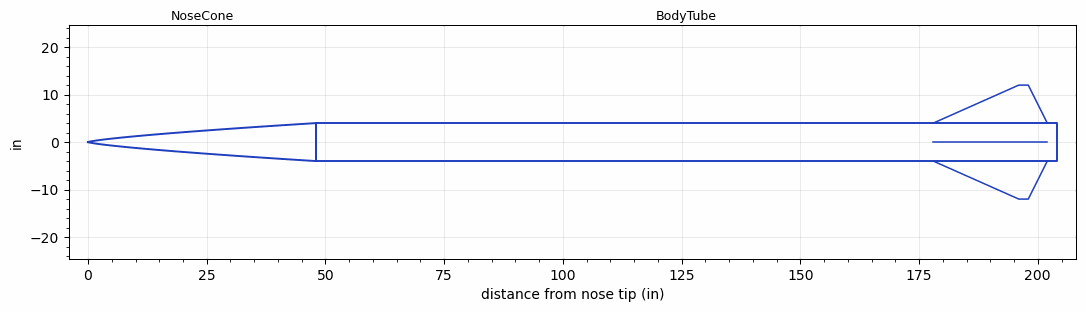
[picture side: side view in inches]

<RASAeroDocument>
 <FileVersion>2</FileVersion>
 <RocketDesign>
  <NoseCone>
   <Length>48</Length>
   <Diameter>8</Diameter>
   <Shape>Power Law</Shape>
   <Location>0</Location>
   <PowerLaw>0.75</PowerLaw>
  </NoseCone>
  <BodyTube>
   <Length>156</Length>
   <Diameter>8</Diameter>
   <Location>48</Location>
   <Fin>
    <Count>4</Count>
    <Chord>24</Chord>
    <Span>8</Span>
    <SweepDistance>18</SweepDistance>
    <TipChord>2</TipChord>
    <Thickness>0.25</Thickness>
    <Location>26</Location>
    <AirfoilSection>Rounded</AirfoilSection>
   </Fin>
  </BodyTube>
  <Surface>Smooth (Zero Roughness)</Surface>
  <ModifiedBarrowman>False</ModifiedBarrowman>
  <Turbulence>False</Turbulence>
  <UseBooster1>False</UseBooster1>
  <UseBooster2>False</UseBooster2>
 </RocketDesign>
 <LaunchSite>
  <Altitude>0</Altitude>
  <Pressure>0</Pressure>
  <RodAngle>0</RodAngle>
  <RodLength>4</RodLength>
  <Temperature>74</Temperature>
  <WindSpeed>0</WindSpeed>
 </LaunchSite>
 <Recovery>
  <Altitude1>1000</Altitude1>
  <Altitude2>1000</Altitude2>
  <DeviceType1>None</DeviceType1>
  <DeviceType2>None</DeviceType2>
  <Event1>False</Event1>
  <Event2>False</Event2>
  <Size1>1</Size1>
  <Size2>1</Size2>
  <EventType1>None</EventType1>
  <EventType2>None</EventType2>
  <CD1>1.33</CD1>
  <CD2>1.33</CD2>
 </Recovery>
 <SimulationList>
  <Simulation>
   <SustainerEngine>Q19134  (TRC)</SustainerEngine>
   <SustainerLaunchWt>250</SustainerLaunchWt>
   <SustainerNozzleDiameter>5.618</SustainerNozzleDiameter>
   <SustainerCG>100</SustainerCG>
   <SustainerIgnitionDelay>0</SustainerIgnitionDelay>
   <Booster1SeparationDelay>0</Booster1SeparationDelay>
   <Booster1IgnitionDelay>0</Booster1IgnitionDelay>
   <IncludeBooster1>False</IncludeBooster1>
   <Booster2Delay>0</Booster2Delay>
   <IncludeBooster2>False</IncludeBooster2>
   <TimetoApogee>122.3877</TimetoApogee>
   <MaxAltitude>230178.3</MaxAltitude>
   <MaxVelocity>5143.687</MaxVelocity>
   <OptimumWt>171.8183</OptimumWt>
   <OptimumMaxAlt>171.8183</OptimumMaxAlt>
  </Simulation>
 </SimulationList>
</RASAeroDocument>
